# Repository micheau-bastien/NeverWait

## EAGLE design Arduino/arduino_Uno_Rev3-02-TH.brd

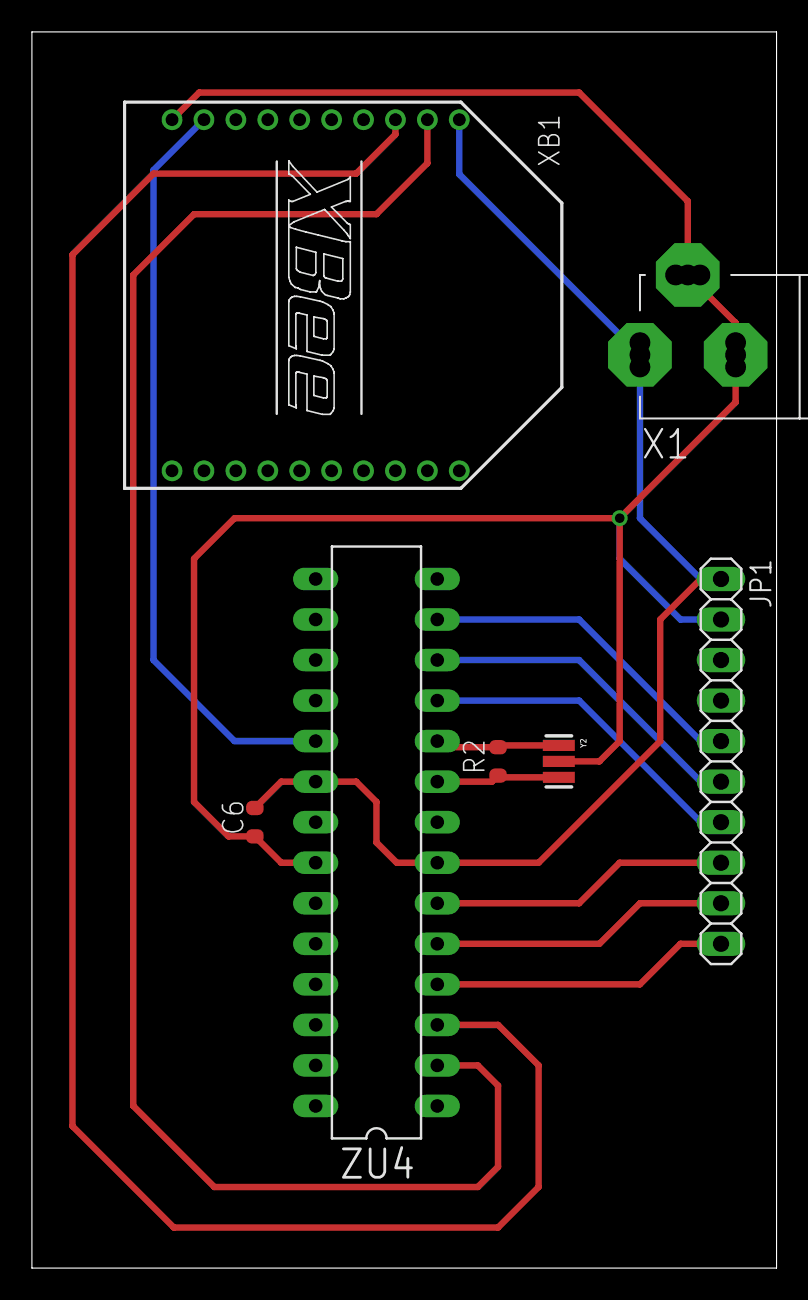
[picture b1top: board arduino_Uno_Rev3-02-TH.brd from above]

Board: 2 copper layers, 46.7 x 77.5 mm, 7 parts (0 on the bottom side), 13 nets.

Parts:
C6: 100n; C0603-ROUND
JP1: 1X10
R2: 1M; R0603-ROUND
X1: POWERSUPPLY_DC21MMX; POWERSUPPLY_DC-21MM
XB1: XBEE
Y2: CSTCE16M0V53-R0 16MHZ; RESONATOR
ZU4: ATMEGA328P-PU; DIL28-3

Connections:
GND: C6.1, X1.1, X1.3, XB1.10, Y2.2, ZU4.8, ZU4.22
unnamed: XB1.3, ZU4.3
unnamed: JP1.10, ZU4.4
unnamed: XB1.2, ZU4.2
unnamed: JP1.5, ZU4.13
unnamed: JP1.8, ZU4.6
unnamed: JP1.7, ZU4.11
unnamed: JP1.6, ZU4.12
unnamed: JP1.9, ZU4.5
unnamed: XB1.9, ZU4.19
VCC: C6.2, JP1.1, X1.2, XB1.1, ZU4.7, ZU4.20
XTAL1: R2.1, Y2.3, ZU4.9
XTAL2: R2.2, Y2.1, ZU4.10

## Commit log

2017-01-25 Comments and new format for time to the back-end
2017-01-25 Edit month for formatted view to be ok with date system of python
2017-01-26 Raspberry Pi code
2017-01-26 Arduino Code
